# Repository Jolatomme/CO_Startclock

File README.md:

# Orienteering Start Clock synchronized to DCF77

Equity in sport is a key point during competition. In orienteering, equity is not guaranteed — start time differs per category and per racer. The start clock has no synchronization with the finish clock (managed by the punching system). Two unsynchronized clocks will drift and introduce uncertainty in effective race time. This project solves that problem by keeping the start clock synchronized to the absolute time delivered by the DCF77 signal.

More details on the [project Wiki](https://github.com/Jolatomme/CO_Startclock/wiki).

## Features

- Synchronizes to DCF77 time signal (German longwave, 77.5 kHz)
- Falls back to internal RTC when DCF77 signal is unavailable
- Real-time display on MAX7219 LED dot matrix (64x8)
- Automatic DST (summer/winter time) handling
- Built on MicroPython for rapid prototyping

## Hardware Requirements

| Component | Description |
|---|---|
| Microcontroller | STM32 Nucleo-64 board (see [supported boards](https://github.com/Jolatomme/CO_Startclock/wiki#micro-controller-platform)) |
| DCF77 receiver | Standard DCF77 module with antenna (e.g., DCF77-1, Hama, etc.) |
| Display | MAX7219-based 8x8 LED dot matrix, 8 modules chained (64x8) |
| Power | USB or external 5V supply |

## Pin Connections

| Nucleo Pin | Connection |
|---|---|
| D4 | DCF77 receiver TCO (time signal output) |
| D7 | MAX7219 CS (chip select) |
| SPI2 SCK | MAX7219 CLK |
| SPI2 MOSI | MAX7219 DIN |
| 3.3V / 5V | DCF77 receiver VCC |
| GND | Common ground |

## Getting Started

### 1. Install MicroPython

Download the latest MicroPython firmware for your board from [micropython.org](https://micropython.org/download/) and flash it using the STM32 Cube Programmer or DFU mode.

### 2. Upload the firmware

```bash
# Using ampy
ampy --port COM3 put boot.py
ampy --port COM3 put main.py
ampy --port COM3 put dcf77.py
ampy --port COM3 put max7219.py

# Or using rshell
rshell -p COM3 cp *.py /pyboard/
```

### 3. Wire the components

Refer to the [Fritzing layout](Fritzing/CO_Clock.fzz) or the [KiCad schematics](StartClock/StartClock.kicad_sch) for detailed wiring.

### 4. Power on

The clock will synchronize with DCF77 and display the current time. The onboard LED blinks once per second and stays on during the last 10 seconds of each minute.

## Project Structure

```
├── nucleo_flash/          # MicroPython firmware
│   ├── boot.py            # Boot configuration
│   ├── main.py            # Main application (async RTC + display)
│   ├── dcf77.py           # DCF77 signal decoder
│   ├── max7219.py         # MAX7219 LED matrix driver
│   └── ds18x20.py         # DS18X20 temperature sensor driver
├── StartClock/            # KiCad hardware design
│   ├── StartClock.kicad_sch   # Schematic
│   ├── StartClock.kicad_pcb   # PCB layout
│   └── StartClock.kicad_pro   # Project file
├── Fritzing/              # Breadboard layout
│   └── CO_Clock.fzz
├── Img/                   # Images
├── README.md
└── LICENSE                # MIT
```

## Project example on a single-sided stripboard

## License

This project is licensed under the [MIT License](LICENSE).

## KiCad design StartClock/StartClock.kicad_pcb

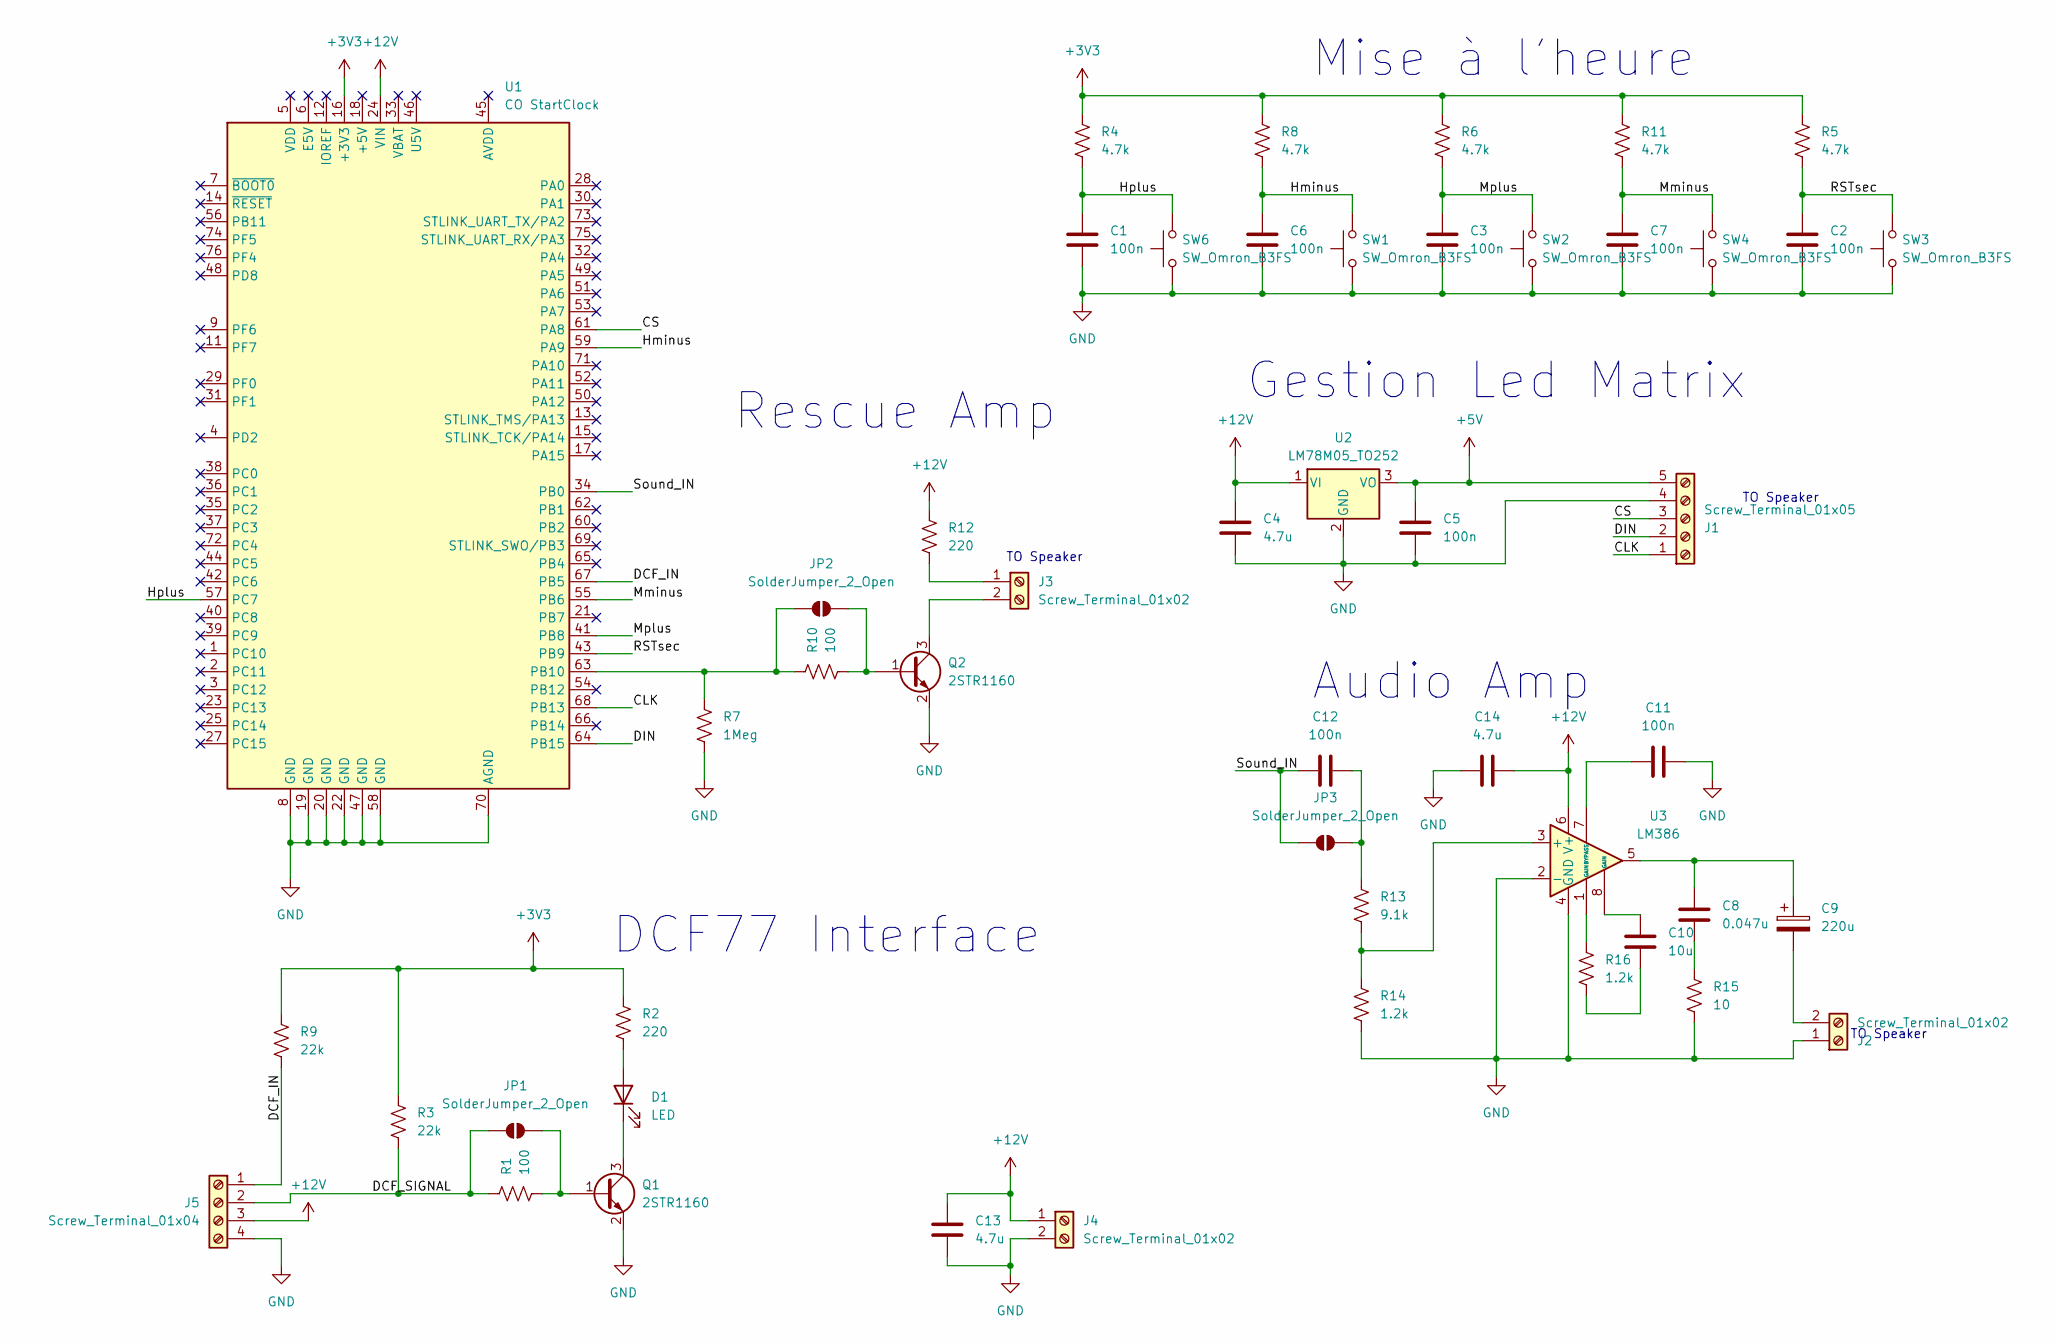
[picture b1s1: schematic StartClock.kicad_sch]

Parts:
C1, C2, C3, C5, C6, C7, C11, C12: 100n; C_0805_2012Metric_Pad1.18x1.45mm_HandSolder
C4, C13, C14: 4.7u; C_0805_2012Metric_Pad1.18x1.45mm_HandSolder
C8: 0.047u; C_0805_2012Metric_Pad1.18x1.45mm_HandSolder
C9: 220u; CP_Radial_D10.0mm_P5.00mm
C10: 10u; C_0805_2012Metric_Pad1.18x1.45mm_HandSolder
D1: LED; LED_0805_2012Metric_Pad1.15x1.40mm_HandSolder
J1: Screw_Terminal_01x05; TerminalBlock_Phoenix_MPT-0,5-5-2.54_1x05_P2.54mm_Horizontal
J2, J3, J4: Screw_Terminal_01x02; TerminalBlock_Phoenix_MPT-0,5-2-2.54_1x02_P2.54mm_Horizontal
J5: Screw_Terminal_01x04; TerminalBlock_Phoenix_MPT-0,5-4-2.54_1x04_P2.54mm_Horizontal
JP1, JP2, JP3: SolderJumper_2_Open; SolderJumper-TrianglePad1.0x1.5mm
Q1, Q2: 2STR1160; TSOT-23
R1, R10: 100; R_0805_2012Metric_Pad1.20x1.40mm_HandSolder
R2: 220; R_0805_2012Metric_Pad1.20x1.40mm_HandSolder
R3, R9: 22k; R_0805_2012Metric_Pad1.20x1.40mm_HandSolder
R4, R5, R6, R8, R11: 4.7k; R_0805_2012Metric_Pad1.20x1.40mm_HandSolder
R7: 1Meg; R_0805_2012Metric_Pad1.20x1.40mm_HandSolder
R12: 220; R_2512_6332Metric
R13: 9.1k; R_0805_2012Metric_Pad1.20x1.40mm_HandSolder
R14, R16: 1.2k; R_0805_2012Metric_Pad1.20x1.40mm_HandSolder
R15: 10; R_0805_2012Metric_Pad1.20x1.40mm_HandSolder
SW1, SW2, SW3, SW4, SW6: SW_Omron_B3FS; SW_SPST_Omron_B3FS-101xP
U1: CO StartClock; ST_Morpho_Connector_64_NOHOLES_TOP
U2: LM78M05_TO252; TO-252-2
U3: LM386; SOIC-8_3.9x4.9mm_P1.27mm

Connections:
+3V3: R2.2, R3.2, R4.2, R5.2, R6.2, R8.2, R9.2, R11.2, U1.16 (+3V3)
+5V: C5.1, J1.5, U2.3 (VO)
+12V: C4.1, C13.1, C14.1, J4.1, J5.3, R12.2, U1.24 (VIN), U2.1 (VI), U3.6 (V+)
/CLK: J1.1, U1.68 (PB13)
/CS: J1.3, U1.61 (PA8)
/DCF_IN: J5.1, R9.1, U1.67 (PB5)
/DCF_SIGNAL: J5.2, JP1.1 (A), R1.1, R3.1
/DIN: J1.2, U1.64 (PB15)
/Hminus: C6.1, R8.1, SW1.2, U1.59 (PA9)
/Hplus: C1.1, R4.1, SW6.2, U1.57 (PC7)
/Mminus: C7.1, R11.1, SW4.2, U1.55 (PB6)
/Mplus: C3.1, R6.1, SW2.2, U1.41 (PB8)
/RSTsec: C2.1, R5.1, SW3.2, U1.43 (PB9)
/Sound_IN: C12.1, JP3.1 (A), U1.34 (PB0)
GND: C1.2, C2.2, C3.2, C4.2, C5.2, C6.2, C7.2, C11.2, C13.2, C14.2, J1.4, J2.1, J4.2, J5.4, Q1.2 (E), Q2.2 (E), R7.1, R14.1, R15.1, SW1.1, SW2.1, SW3.1, SW4.1, SW6.1, U1.8 (GND), U1.19 (GND), U1.20 (GND), U1.22 (GND), U1.47 (GND), U1.58 (GND), U1.70 (AGND), U2.2 (GND), U3.2 (-), U3.4 (GND)
unnamed: C8.1, C9.1, U3.5
unnamed: C8.2, R15.2
unnamed: C10.1, U3.8 (GAIN)
unnamed: C10.2, R16.1
unnamed: D1.2 (A), R2.1
unnamed: D1.1 (K), Q1.3 (C)
unnamed: C9.2, J2.2
unnamed: J3.1, R12.1
unnamed: J3.2, Q2.3 (C)
unnamed: JP1.2 (B), Q1.1 (B), R1.2
unnamed: JP2.1 (A), R7.2, R10.1, U1.63 (PB10)
unnamed: JP2.2 (B), Q2.1 (B), R10.2
unnamed: C12.2, JP3.2 (B), R13.2
unnamed: R16.2, U3.1 (GAIN)
unnamed: R13.1, R14.2, U3.3 (+)
unnamed: C11.1, U3.7 (BYPASS)

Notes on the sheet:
TO Speaker
Audio Amp
Rescue Amp
DCF77 Interface
Mise à l'heure
Gestion Led Matrix

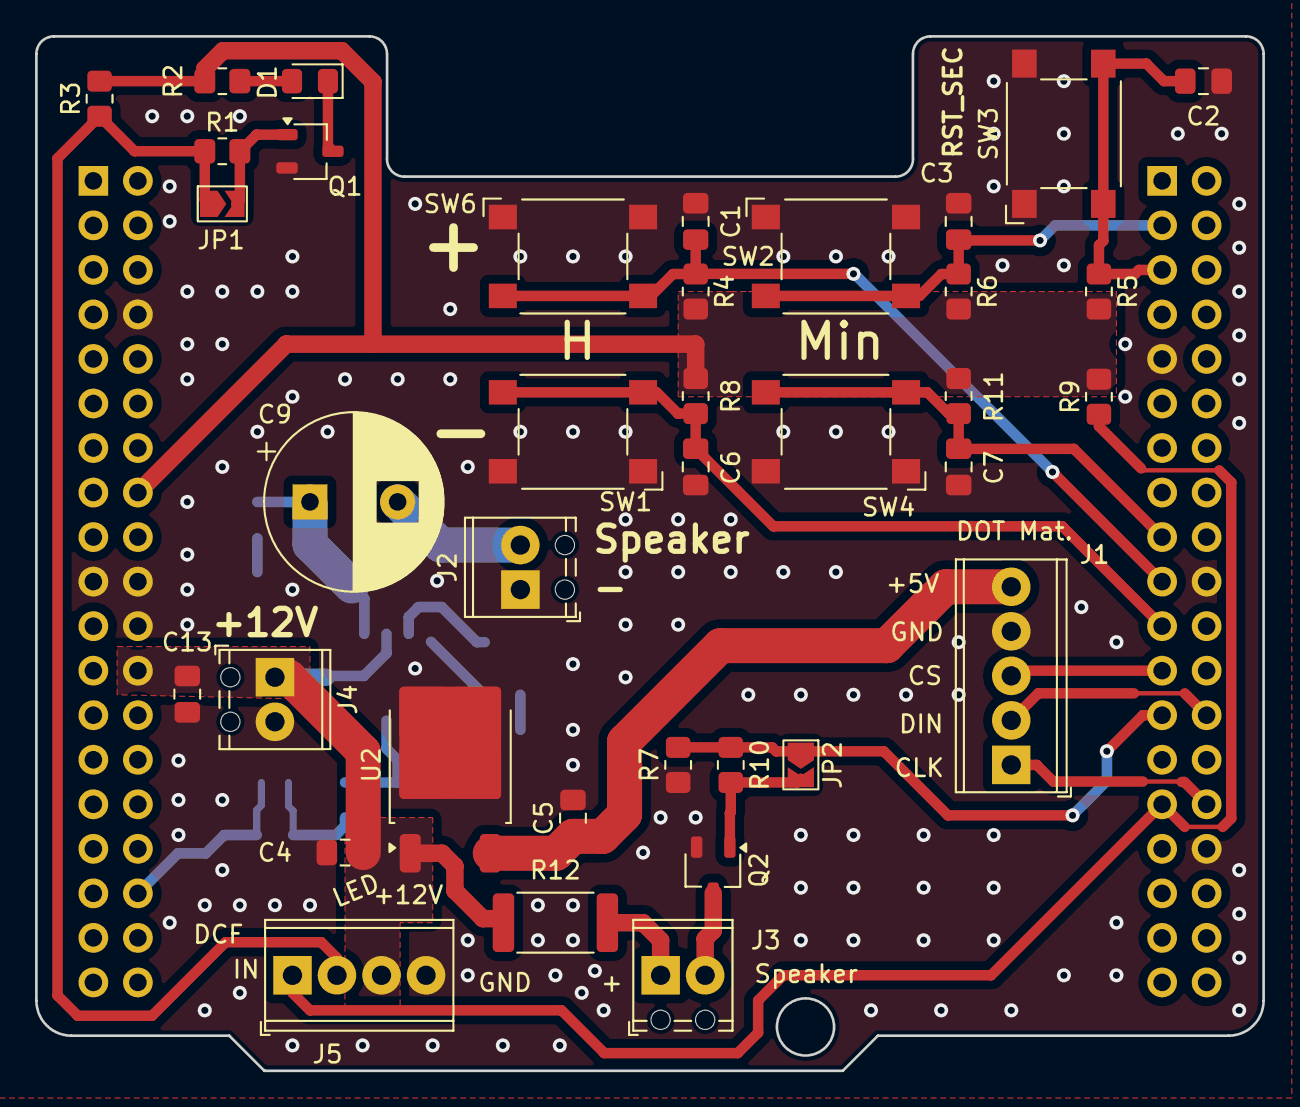
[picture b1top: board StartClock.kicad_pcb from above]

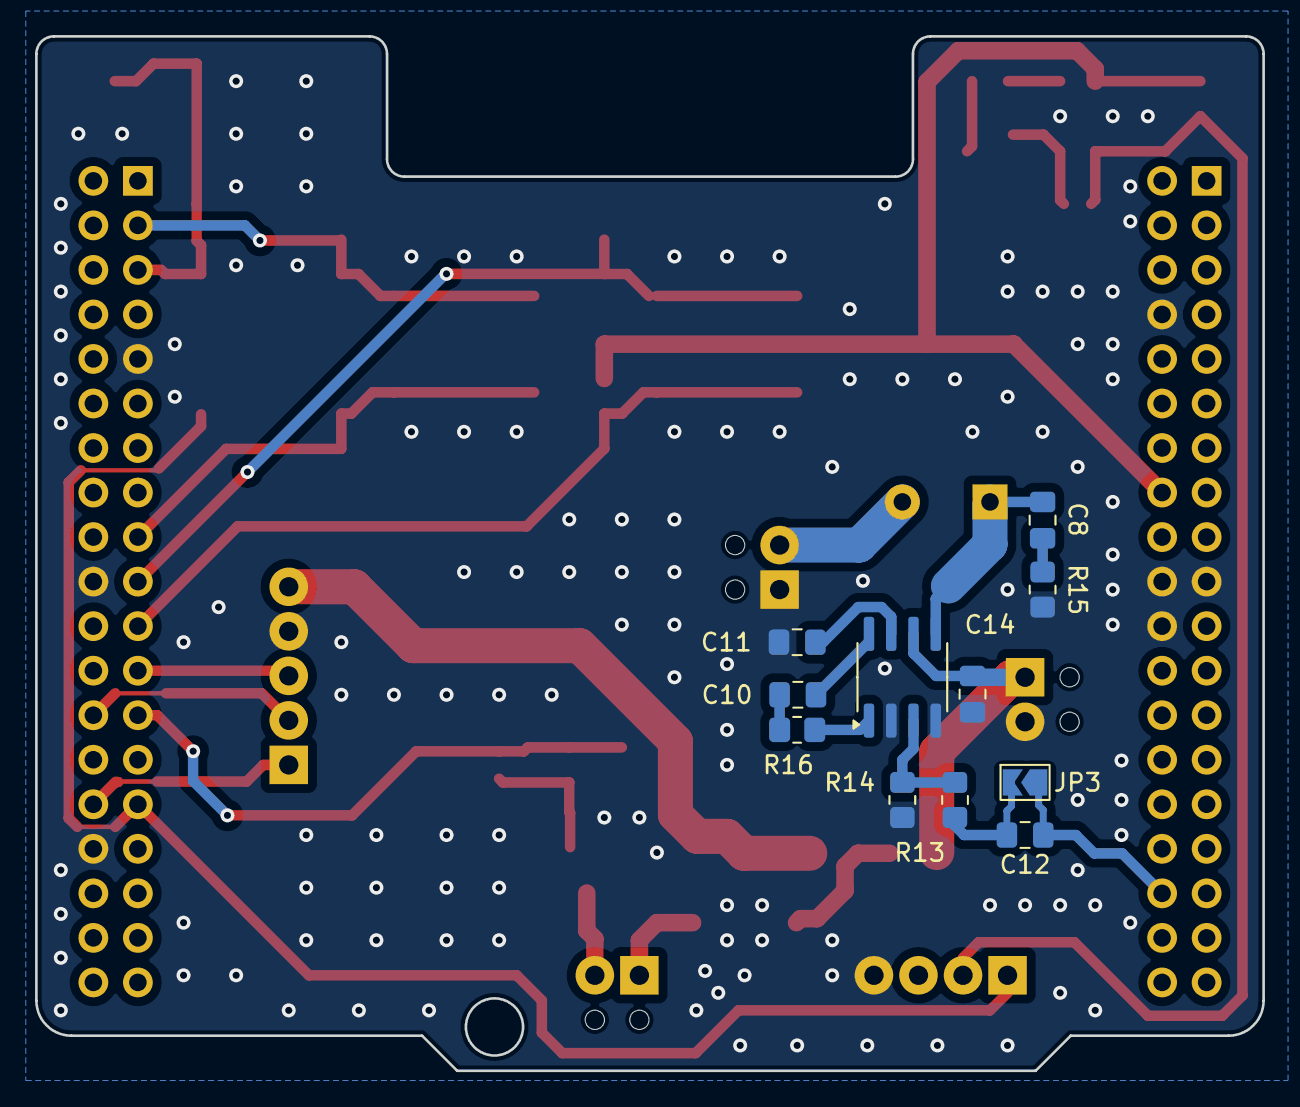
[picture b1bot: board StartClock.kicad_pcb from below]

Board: 2 copper layers, 70.0 x 59.0 mm, 49 parts (11 on the bottom side), 31 nets.

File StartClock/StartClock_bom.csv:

"Reference","Value","Footprint","Qty","DNP","Ref mouser","Description"
"C1,C2,C3,C5,C6,C7,C11,C12","100n","Capacitor_SMD:C_0805_2012Metric_Pad1.18x1.45mm_HandSolder","8","","https://www.mouser.fr/ProductDetail/KEMET/C0805C104K6RACTU?q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","Unpolarized capacitor"
"C4,C13,C14","4.7u","Capacitor_SMD:C_0805_2012Metric_Pad1.18x1.45mm_HandSolder","3","","https://www.mouser.fr/ProductDetail/Murata-Electronics/GRM21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","Unpolarized capacitor"
"C8","0.047u","Capacitor_SMD:C_0805_2012Metric_Pad1.18x1.45mm_HandSolder","1","","https://www.mouser.fr/ProductDetail/KYOCERA-AVX/08053C473KAT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","Unpolarized capacitor"
"C9","220u","Capacitor_THT:CP_Radial_D10.0mm_P5.00mm","1","","None: in Stock","Polarized capacitor"
"C10","10u","Capacitor_SMD:C_0805_2012Metric_Pad1.18x1.45mm_HandSolder","1","","https://www.mouser.fr/ProductDetail/Murata-Electronics/GRM21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","Unpolarized capacitor"
"D1","LED","LED_SMD:LED_0805_2012Metric_Pad1.15x1.40mm_HandSolder","1","","https://www.mouser.fr/ProductDetail/Wurth-Elektronik/150080S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","Light emitting diode"
"J1","Screw_Terminal_01x05","TerminalBlock_Phoenix:TerminalBlock_Phoenix_MPT-0,5-5-2.54_1x05_P2.54mm_Horizontal","1","","https://www.mouser.fr/ProductDetail/Wurth-Elektronik/6912109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","Generic screw terminal, single row, 01x05, script generated (kicad-library-utils/schlib/autogen/connector/)"
"J2,J3,J4","Screw_Terminal_01x02","TerminalBlock_Phoenix:TerminalBlock_Phoenix_MPT-0,5-2-2.54_1x02_P2.54mm_Horizontal","3","","https://www.mouser.fr/ProductDetail/Wurth-Elektronik/6912109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","Generic screw terminal, single row, 01x02, script generated (kicad-library-utils/schlib/autogen/connector/)"
"J5","Screw_Terminal_01x04","TerminalBlock_Phoenix:TerminalBlock_Phoenix_MPT-0,5-4-2.54_1x04_P2.54mm_Horizontal","1","","https://www.mouser.fr/ProductDetail/Wurth-Elektronik/6912109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","Generic screw terminal, single row, 01x04, script generated (kicad-library-utils/schlib/autogen/connector/)"
"Q1,Q2","2STR1160","Package_TO_SOT_SMD:TSOT-23","2","","None: in Stock","NPN transistor, base/emitter/collector"
"R1,R10","100","Resistor_SMD:R_0805_2012Metric_Pad1.20x1.40mm_HandSolder","2","","https://www.mouser.fr/ProductDetail/YAGEO/RT0805DRD07100RL?q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","Resistor, US symbol"
"R2,R12","220","-- valeurs mixtées --","2","","-- valeurs mixtées --","Resistor, US symbol"
"R3,R9","22k","Resistor_SMD:R_0805_2012Metric_Pad1.20x1.40mm_HandSolder","2","","https://www.mouser.fr/ProductDetail/YAGEO/RT0805FRE1322KL?qs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","Resistor, US symbol"
"R4,R5,R6,R8,R11","4.7k","Resistor_SMD:R_0805_2012Metric_Pad1.20x1.40mm_HandSolder","5","","https://www.mouser.fr/ProductDetail/YAGEO/RC0805FR-074K7L?qs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","Resistor, US symbol"
"R7","1Meg","Resistor_SMD:R_0805_2012Metric_Pad1.20x1.40mm_HandSolder","1","","https://www.mouser.fr/ProductDetail/YAGEO/RT0805FRE101ML?qs=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","Resistor, US symbol"
"R13","9.1k","Resistor_SMD:R_0805_2012Metric_Pad1.20x1.40mm_HandSolder","1","","https://www.mouser.fr/ProductDetail/YAGEO/RT0805FRE079K1L?qs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","Resistor, US symbol"
"R14,R16","1.2k","Resistor_SMD:R_0805_2012Metric_Pad1.20x1.40mm_HandSolder","2","","https://www.mouser.fr/ProductDetail/YAGEO/RT0805FRE071K2L?qs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","Resistor, US symbol"
"R15","10","Resistor_SMD:R_0805_2012Metric_Pad1.20x1.40mm_HandSolder","1","","https://www.mouser.fr/ProductDetail/YAGEO/RT0805FRE1310RL?qs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","Resistor, US symbol"
"SW1,SW2,SW3,SW4,SW6","SW_Omron_B3FS","Button_Switch_SMD:SW_SPST_Omron_B3FS-101xP","5","","https://www.mouser.fr/ProductDetail/Omron-Electronics/B3FS-1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","Omron B3FS 6x6mm single pole normally-open tactile switch"
"U1","CO StartClock","Nucleo_64:ST_Morpho_Connector_64_NOHOLES_TOP","1","","None: in Stock","Nucleo 64 Development Board with STM32L152RE"
"U2","LM78M05_TO252","Package_TO_SOT_SMD:TO-252-2","1","","https://www.mouser.fr/ProductDetail/STMicroelectronics/L7805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","Positive 500mA 35V Linear Regulator, Fixed Output 5V, TO-252 (D-PAK)"
"U3","LM386","Package_SO:SOIC-8_3.9x4.9mm_P1.27mm","1","","https://www.mouser.fr/ProductDetail/Texas-Instruments/LM386M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","Low Voltage Audio Power Amplifier, DIP-8/SOIC-8/SSOP-8"

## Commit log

2024-04-10 Initial falsh content
2024-04-10 Readme added
2024-04-10 Updated from Nucleo download
2024-04-10 MAX7219 testing
2024-04-11 Readme redaction
2024-04-11 Section moved to Wiki
2024-04-12 corrected link to wiki
2024-04-12 Corrected screen size
2024-04-12 Removed unecessary prev_min and prev_hour
2024-04-20 Succes verrouillage heure
2024-04-21 Asynchronous version of main added
2024-04-24 Removed self in independant Tasks
2024-04-24 removed RTC from DCF class
2024-04-27 Functional async clock
2024-04-27 removed comments
2024-05-05 Added Clock Schematics done with Fritzing
2024-05-05 Corrected link to Fritzing Image
2024-05-05 typo correction
2024-05-07 First version for Nucelo Shield with KiCad
2024-05-07 gitognore added
2024-05-07 Components updates after Mouser ordering few parts changed due to unavailability
2024-05-07 After Aisler PCB order
2024-05-12 Added extra filtering
2024-05-12 Aisler number removed for sharing
2026-03-20 Add MIT License to the project
